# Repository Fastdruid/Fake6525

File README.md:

# Fake6525

This was forked from ZXByteman/Fake6523 which is a MOS 6523 TPI (Tri Port Interface) CPLD replacement which has been proved on a 1551.

This itself was a fork of the original go4retro/Fake6523 repo from which the "Code was fixed and HW checked on real 1551 - working good."

As the 6525 behaves exactly as a 6523 when in "Mode 0" but has two additional registers and a second Mode 1 where it has added interrupts, handshaking pins and GPIO pins. I've attempted to rewrite to add the additional registers and behave as a 6525. 

I have changed the Eagle board and schematics to KiCAD. There are no changes however as the hardware is identical (same pin outs) so while KiCAD is my "preferred" program feel free to use the Eagle versions if you prefer. 

In theory this should probably work. Maybe.

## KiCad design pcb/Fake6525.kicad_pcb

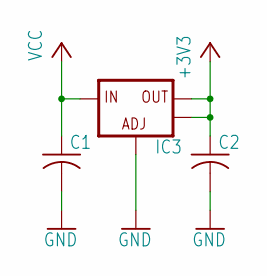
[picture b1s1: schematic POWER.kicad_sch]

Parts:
C1, C2: C-USC0805; C0805
IC3: V_REG_LM1117SOT223; SOT223

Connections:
+3V3: C2.1, IC3.2 (OUT), IC3.4 (OUT@1); also elsewhere on the board
GND: C1.2, C2.2, IC3.1 (ADJ); also elsewhere on the board
VCC: C1.1, IC3.3 (IN); also elsewhere on the board

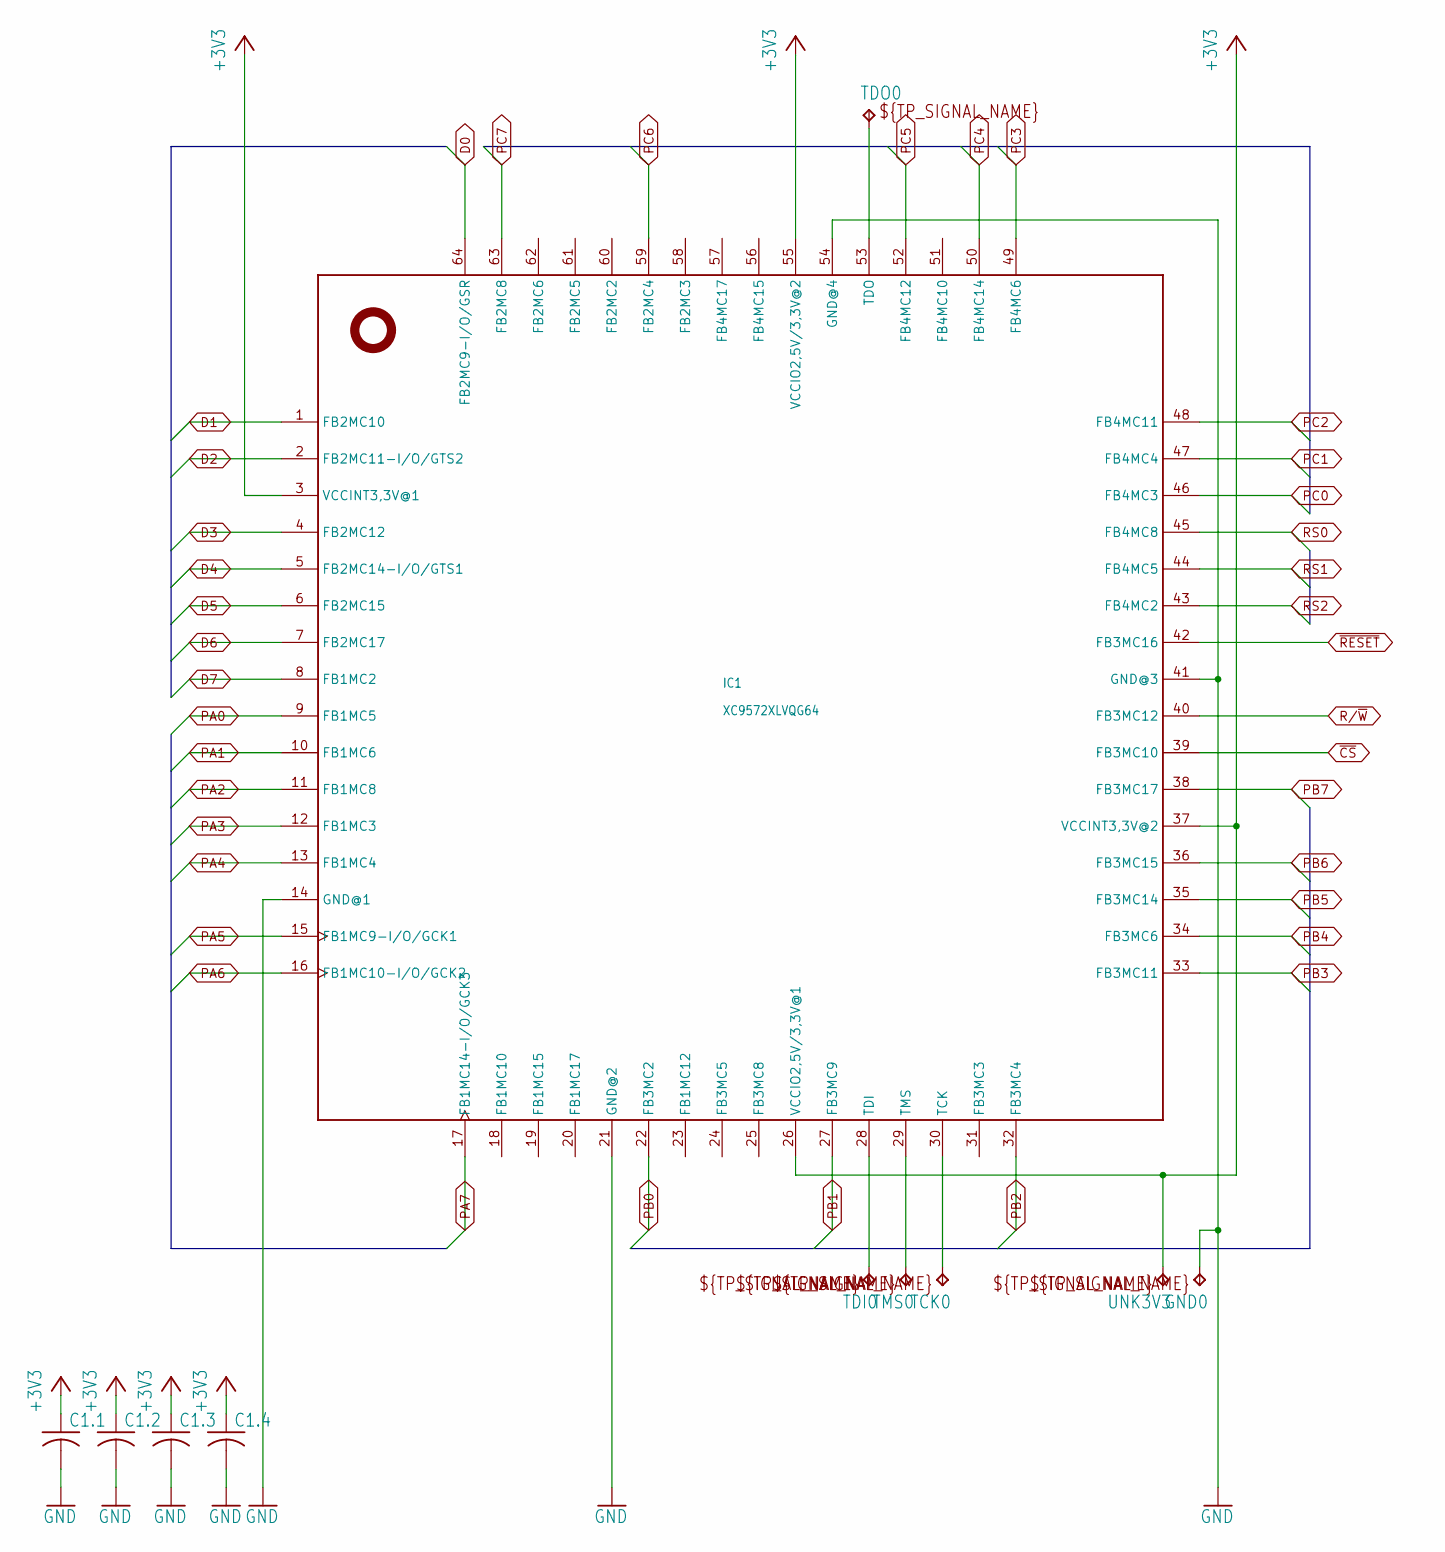
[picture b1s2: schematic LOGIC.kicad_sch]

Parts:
C1.1, C1.2, C1.3, C1.4: C-USC0402; C0402
GND0: TPTP08R; TP08R
IC1: XC9572XLVQG64; VQFP64
TCK0: TPTP08R; TP08R
TDI0: TPTP08R; TP08R
TDO0: TPTP08R; TP08R
TMS0: TPTP08R; TP08R
UNK3V3: TPTP08R; TP08R

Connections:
+3V3: C1.1.1, C1.2.1, C1.3.1, C1.4.1, IC1.3 (VCCINT3,3V@1), IC1.26 (VCCIO2,5V/3,3V@1), IC1.37 (VCCINT3,3V@2), IC1.55 (VCCIO2,5V/3,3V@2), UNK3V3.TP; also elsewhere on the board
D0: IC1.64 (FB2MC9-I/O/GSR); also elsewhere on the board
D1: IC1.1 (FB2MC10); also elsewhere on the board
D2: IC1.2 (FB2MC11-I/O/GTS2); also elsewhere on the board
D3: IC1.4 (FB2MC12); also elsewhere on the board
D4: IC1.5 (FB2MC14-I/O/GTS1); also elsewhere on the board
D5: IC1.6 (FB2MC15); also elsewhere on the board
D6: IC1.7 (FB2MC17); also elsewhere on the board
D7: IC1.8 (FB1MC2); also elsewhere on the board
GND: C1.1.2, C1.2.2, C1.3.2, C1.4.2, GND0.TP, IC1.14 (GND@1), IC1.21 (GND@2), IC1.41 (GND@3), IC1.54 (GND@4); also elsewhere on the board
PA0: IC1.9 (FB1MC5); also elsewhere on the board
PA1: IC1.10 (FB1MC6); also elsewhere on the board
PA2: IC1.11 (FB1MC8); also elsewhere on the board
PA3: IC1.12 (FB1MC3); also elsewhere on the board
PA4: IC1.13 (FB1MC4); also elsewhere on the board
PA5: IC1.15 (FB1MC9-I/O/GCK1); also elsewhere on the board
PA6: IC1.16 (FB1MC10-I/O/GCK2); also elsewhere on the board
PA7: IC1.17 (FB1MC14-I/O/GCK3); also elsewhere on the board
PB0: IC1.22 (FB3MC2); also elsewhere on the board
PB1: IC1.27 (FB3MC9); also elsewhere on the board
PB2: IC1.32 (FB3MC4); also elsewhere on the board
PB3: IC1.33 (FB3MC11); also elsewhere on the board
PB4: IC1.34 (FB3MC6); also elsewhere on the board
PB5: IC1.35 (FB3MC14); also elsewhere on the board
PB6: IC1.36 (FB3MC15); also elsewhere on the board
PB7: IC1.38 (FB3MC17); also elsewhere on the board
PC0: IC1.46 (FB4MC3); also elsewhere on the board
PC1: IC1.47 (FB4MC4); also elsewhere on the board
PC2: IC1.48 (FB4MC11); also elsewhere on the board
PC3: IC1.49 (FB4MC6); also elsewhere on the board
PC4: IC1.50 (FB4MC14); also elsewhere on the board
PC5: IC1.52 (FB4MC12); also elsewhere on the board
PC6: IC1.59 (FB2MC4); also elsewhere on the board
PC7: IC1.63 (FB2MC8); also elsewhere on the board
R/~W: IC1.40 (FB3MC12); also elsewhere on the board
RS0: IC1.45 (FB4MC8); also elsewhere on the board
RS1: IC1.44 (FB4MC5); also elsewhere on the board
RS2: IC1.43 (FB4MC2); also elsewhere on the board
TCK: IC1.30 (TCK), TCK0.TP
TDI: IC1.28 (TDI), TDI0.TP
TDO: IC1.53 (TDO), TDO0.TP
TMS: IC1.29 (TMS), TMS0.TP
~CS: IC1.39 (FB3MC10); also elsewhere on the board
~RESET: IC1.42 (FB3MC16); also elsewhere on the board

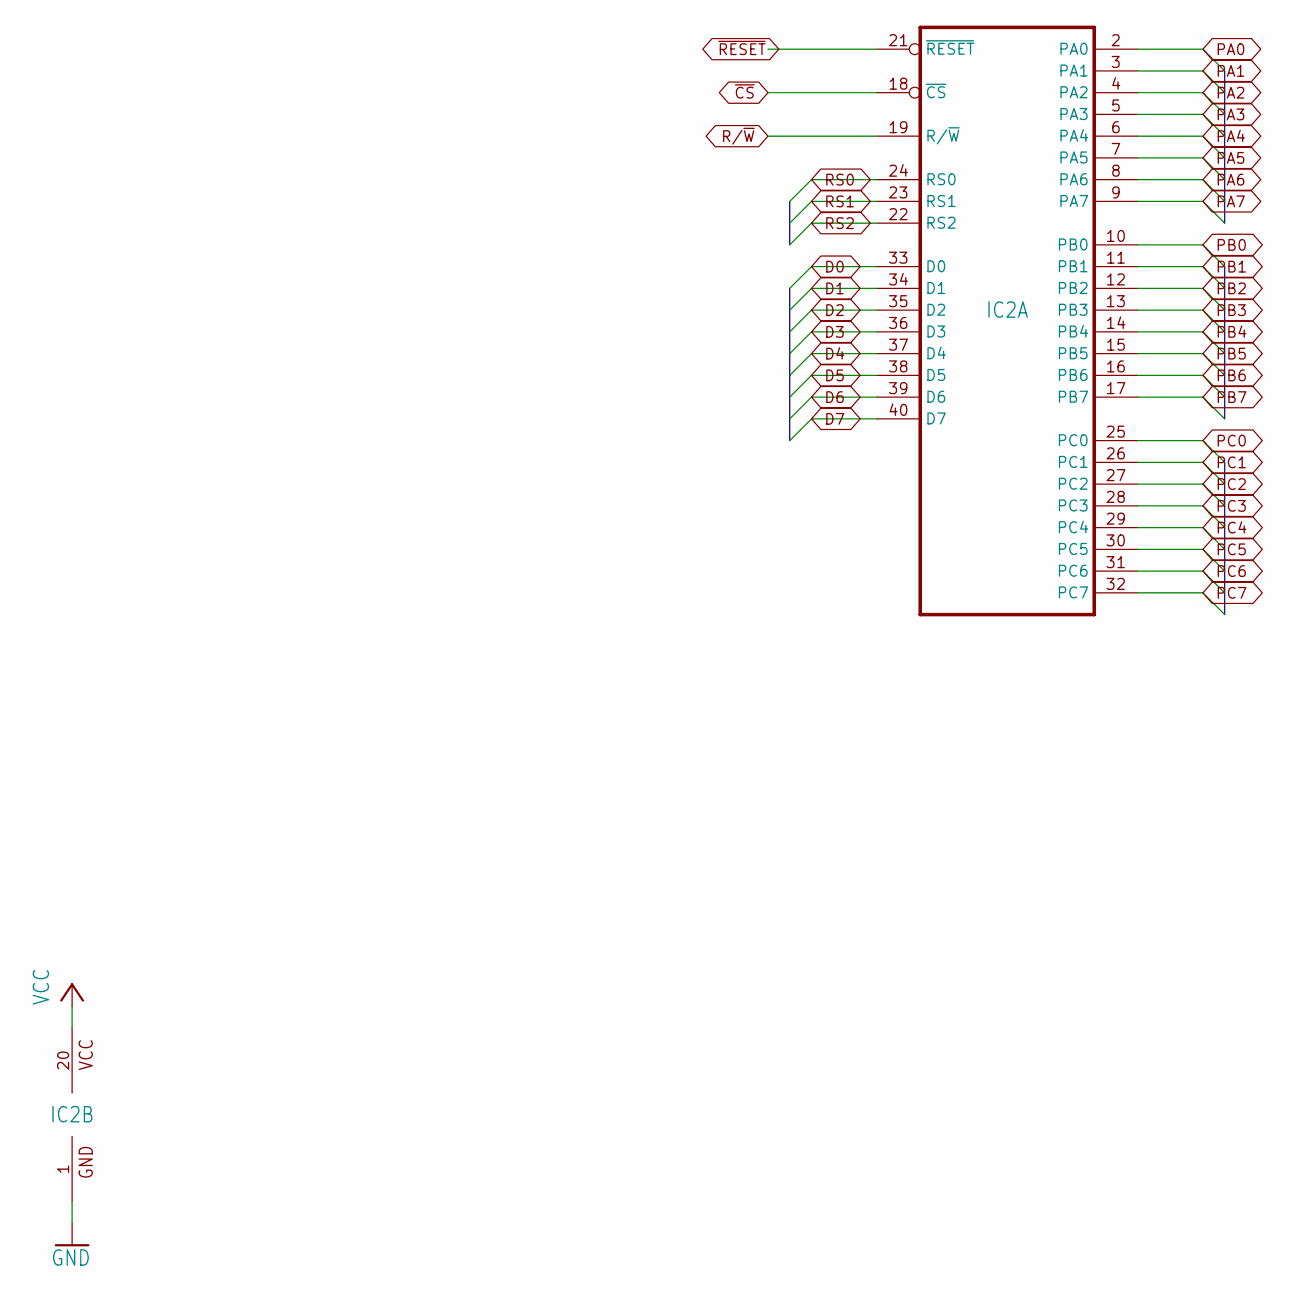
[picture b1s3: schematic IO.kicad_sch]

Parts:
IC2: 6523-R; DIL40-ROUNDPAD

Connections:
D0: IC2.33 (D0); also elsewhere on the board
D1: IC2.34 (D1); also elsewhere on the board
D2: IC2.35 (D2); also elsewhere on the board
D3: IC2.36 (D3); also elsewhere on the board
D4: IC2.37 (D4); also elsewhere on the board
D5: IC2.38 (D5); also elsewhere on the board
D6: IC2.39 (D6); also elsewhere on the board
D7: IC2.40 (D7); also elsewhere on the board
GND: IC2.1 (GND); also elsewhere on the board
PA0: IC2.2 (PA0); also elsewhere on the board
PA1: IC2.3 (PA1); also elsewhere on the board
PA2: IC2.4 (PA2); also elsewhere on the board
PA3: IC2.5 (PA3); also elsewhere on the board
PA4: IC2.6 (PA4); also elsewhere on the board
PA5: IC2.7 (PA5); also elsewhere on the board
PA6: IC2.8 (PA6); also elsewhere on the board
PA7: IC2.9 (PA7); also elsewhere on the board
PB0: IC2.10 (PB0); also elsewhere on the board
PB1: IC2.11 (PB1); also elsewhere on the board
PB2: IC2.12 (PB2); also elsewhere on the board
PB3: IC2.13 (PB3); also elsewhere on the board
PB4: IC2.14 (PB4); also elsewhere on the board
PB5: IC2.15 (PB5); also elsewhere on the board
PB6: IC2.16 (PB6); also elsewhere on the board
PB7: IC2.17 (PB7); also elsewhere on the board
PC0: IC2.25 (PC0); also elsewhere on the board
PC1: IC2.26 (PC1); also elsewhere on the board
PC2: IC2.27 (PC2); also elsewhere on the board
PC3: IC2.28 (PC3); also elsewhere on the board
PC4: IC2.29 (PC4); also elsewhere on the board
PC5: IC2.30 (PC5); also elsewhere on the board
PC6: IC2.31 (PC6); also elsewhere on the board
PC7: IC2.32 (PC7); also elsewhere on the board
R/~W: IC2.19 (R/~W); also elsewhere on the board
RS0: IC2.24 (RS0); also elsewhere on the board
RS1: IC2.23 (RS1); also elsewhere on the board
RS2: IC2.22 (RS2); also elsewhere on the board
VCC: IC2.20 (VCC); also elsewhere on the board
~CS: IC2.18 (~CS); also elsewhere on the board
~RESET: IC2.21 (~RESET); also elsewhere on the board

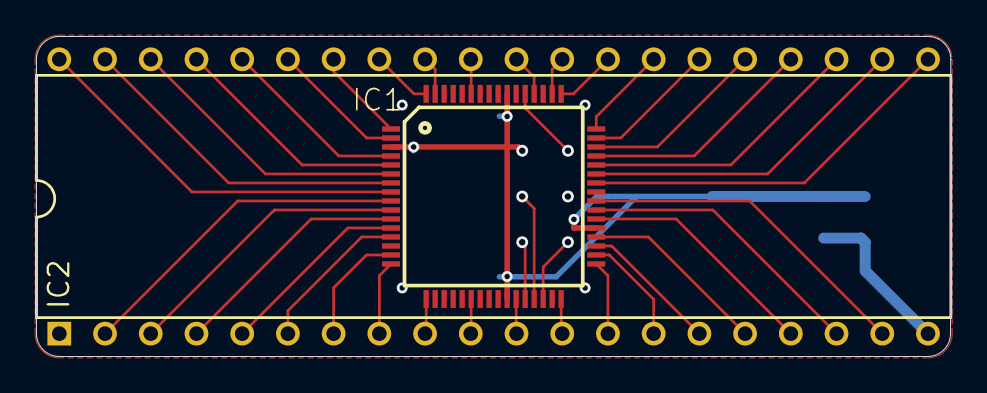
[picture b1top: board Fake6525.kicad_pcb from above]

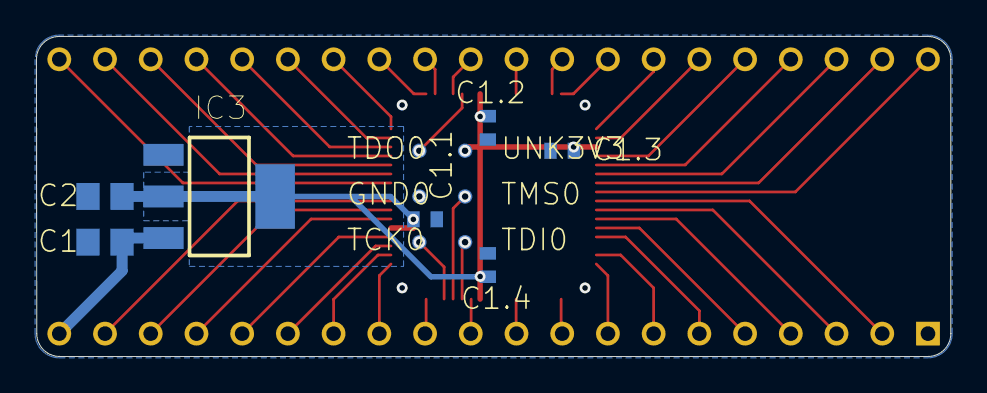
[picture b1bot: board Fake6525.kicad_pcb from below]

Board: 2 copper layers, 50.8 x 17.8 mm, 15 parts (13 on the bottom side), 45 nets.

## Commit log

2023-05-29 Fixes for 1551
2023-05-29 Add JED file
2023-05-29 Add photos
2025-01-11 Added comments to Fake6523.v
2025-01-11 Rename Fake6523.ucf to Fake6525.ucf
2025-01-11 Rename Fake6523.gise to Fake6525.gise
2025-01-11 Rename pcb/Fake6523.brd to pcb/Eagle/Fake6523.brd
2025-01-11 Rename pcb/Fake6523.sch to pcb/Eagle/Fake6523.sch
